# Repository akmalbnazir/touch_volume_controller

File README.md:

# 🔊 Capacitive Touch Volume Controller

A modern, USB-powered capacitive volume controller that uses a single touchpad and an RGB LED to simulate digital volume control behavior. Built with the RP2040 microcontroller, this project integrates capacitive sensing, RGB visual feedback, and optional OLED display output — all designed in **KiCad**.

---

## 🚀 Features

- 🖐️ Capacitive touch input (single-point)
- 🌈 WS2812B RGB LED for visual feedback
- ⚡ USB-C powered (with fuse and Schottky protection)
- 🧠 RP2040 microcontroller core
- 🖥️ Optional 0.96" I²C OLED header
- 🧩 Beginner-friendly, surface-mount layout (SMD)

---

## 🧠 How It Works

- When a user touches the copper pad, the RP2040 measures capacitive charge delay through a 1MΩ resistor.
- The firmware interprets this as a "volume adjust" interaction.
- The RGB LED brightness or color changes to reflect volume level.
- Optionally, volume level can be displayed numerically via OLED.

---

## 📐 Schematic Blocks

### 🔋 Power & Protection
- `J1`: USB-C Receptacle (16-pin)
- `F1`: Resettable PTC fuse
- `D1`: Schottky diode (SS14)
- `C1`: 0.1 µF decoupling capacitor

### 🧠 Microcontroller Core
- `U1`: RP2040 QFN-56
- `Y1`: 3.2x2.5mm crystal (optional)
- `C2–C4`: Bypass and regulator caps (1µF + 0.1µF)
- `R1`: 10kΩ pull-up for RUN pin

### ✋ Touch Sensing
- `TP1`: Touch pad test point
- `R2`: 1MΩ sensing resistor

### 🌈 RGB LED Output
- `D2`: WS2812B (PLCC4)
- `R3`: 330Ω data-line protection
- `C5`: 100 µF bulk cap

### 🖥️ Optional OLED Display
- `J2`: Conn_01x04 (SDA, SCL, GND, 3.3V)
- `R4`, `R5`: 4.7kΩ I²C pull-up resistors

---

## 📦 Bill of Materials (BOM)

| Ref | Value/Part | Notes |
|-----|------------|-------|
| C1 | 0.1 µF | USB input filter |
| C2 | 1 µF | VREG_VOUT cap |
| C3, C4 | 0.1 µF | IOVDD/DVDD bypass |
| C5 | 100 µF | WS2812B power smoothing |
| D1 | Schottky | SS14 or similar |
| D2 | WS2812B | PLCC4 5050 |
| F1 | PTC Fuse | 500mA or similar |
| J1 | USB-C | HRO_TYPE-C-31-M-12 |
| J2 | OLED Header | 1x04, 2.54mm |
| R1 | 10kΩ | RUN pin pull-up |
| R2 | 1MΩ | Capacitive touch |
| R3 | 330Ω | LED data resistor |
| R4, R5 | 4.7kΩ | I²C pull-ups |
| TP1 | Test Point | Touch surface |
| U1 | RP2040 | QFN-56 |
| Y1 | Crystal | 3.2x2.5mm SMD

---

## 🛠️ Getting Started

1. Flash firmware via SWD or USB bootloader
2. Touch pad triggers volume state change
3. LED reflects level (brightness, hue, etc.)
4. (Optional) OLED displays numerical volume level

---

## 📸 Preview

---

## 🧑‍💻 Author

Designed by Akmal Nazir — May 2025  
Built in KiCad 8 — RP2040-powered — USB-C elegance

---

## 🪪 License

MIT License — free to use, remix, and distribute.

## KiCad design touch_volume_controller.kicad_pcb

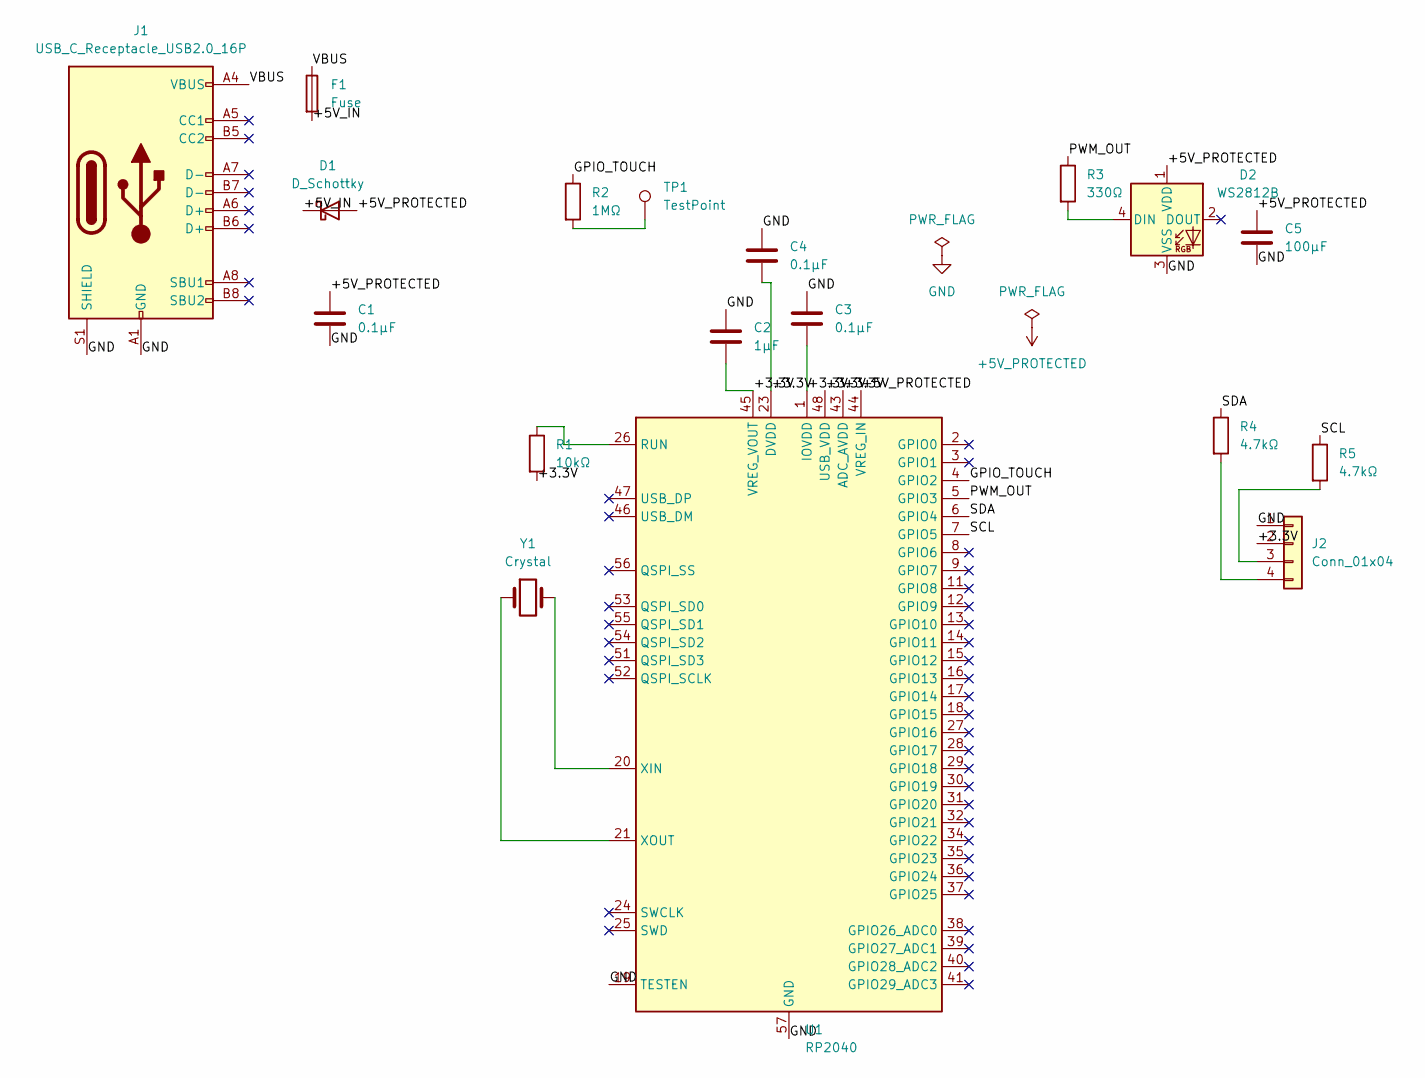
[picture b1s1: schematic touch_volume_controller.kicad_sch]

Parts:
C1, C3, C4: 0.1µF; C_0603_1608Metric
C2: 1µF; C_0805_2012Metric
C5: 100µF; C_1206_3216Metric
D1: D_Schottky; D_SMA
D2: WS2812B; LED_WS2812B_PLCC4_5.0x5.0mm_P3.2mm
F1: Fuse; Fuse_1206_3216Metric
J1: USB_C_Receptacle_USB2.0_16P; USB_C_Receptacle_HRO_TYPE-C-31-M-12
J2: Conn_01x04; PinSocket_1x04_P2.54mm_Vertical
R1: 10kΩ; R_0603_1608Metric
R2: 1MΩ; R_0603_1608Metric
R3: 330Ω; R_0603_1608Metric
R4, R5: 4.7kΩ; R_0603_1608Metric
TP1: TestPoint; TestPoint_Pad_D2.0mm
U1: RP2040; QFN-56-1EP_7x7mm_P0.4mm_EP3.2x3.2mm
Y1: Crystal; Crystal_SMD_3225-4Pin_3.2x2.5mm

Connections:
+5V_PROTECTED: C1.1, C5.1, D1.2 (A), D2.1 (VDD), U1.44 (VREG_IN)
/+3.3V: C2.2, C3.2, C4.2, J2.2, R1.2, U1.1 (IOVDD), U1.10 (IOVDD), U1.22 (IOVDD), U1.23 (DVDD), U1.33 (IOVDD), U1.42 (IOVDD), U1.43 (ADC_AVDD), U1.45 (VREG_VOUT), U1.48 (USB_VDD), U1.49 (IOVDD), U1.50 (DVDD)
/+5V_IN: D1.1 (K), F1.2
/GPIO_TOUCH: R2.1, U1.4 (GPIO2)
/PWM_OUT: R3.1, U1.5 (GPIO3)
/SCL: R5.1, U1.7 (GPIO5)
/SDA: R4.1, U1.6 (GPIO4)
/VBUS: F1.1, J1.A4 (VBUS), J1.A9 (VBUS), J1.B4 (VBUS), J1.B9 (VBUS)
GND: C1.2, C2.1, C3.1, C4.1, C5.2, D2.3 (VSS), J1.A1 (GND), J1.A12 (GND), J1.B1 (GND), J1.B12 (GND), J1.S1 (SHIELD), J2.1, U1.19 (TESTEN), U1.57 (GND)
unnamed: D2.4 (DIN), R3.2
unnamed: J2.3, R5.2
unnamed: J2.4, R4.2
unnamed: R2.2, TP1.1
unnamed: R1.1, U1.26 (RUN)
unnamed: U1.20 (XIN), Y1.2
unnamed: U1.21 (XOUT), Y1.1

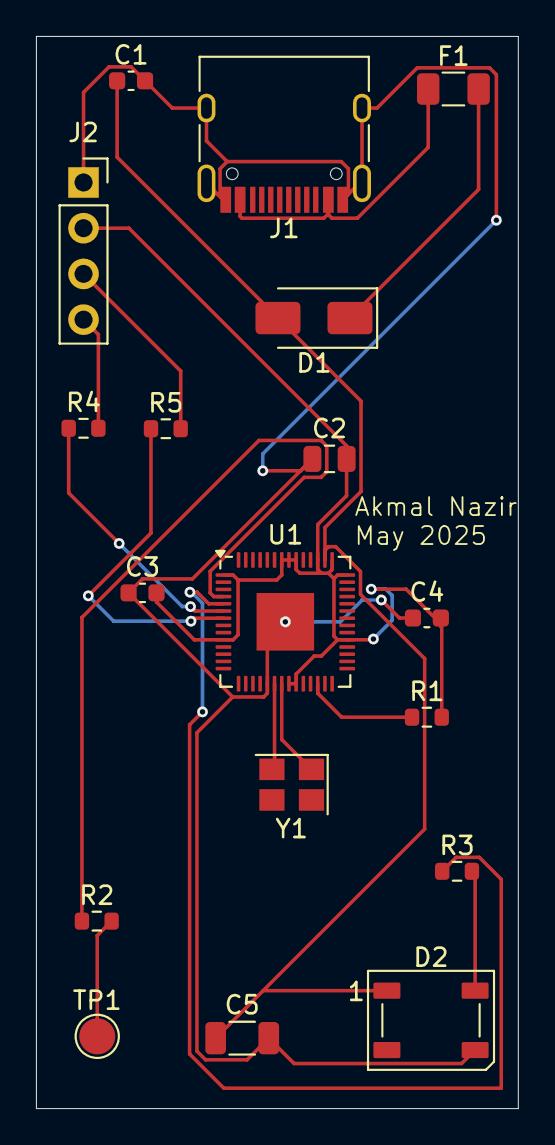
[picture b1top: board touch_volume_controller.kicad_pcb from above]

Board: 2 copper layers, 26.8 x 59.6 mm, 18 parts (0 on the bottom side), 16 nets.

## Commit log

2025-05-15 Origin Commit
